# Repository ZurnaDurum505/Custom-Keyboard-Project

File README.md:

# Custom-Keyboard-Project 
I started my keyboard by starting to make the PCB using Kicad. To do the PCB I had to do the schematics first by placing switches for the keys and adding diodes on every switch so the keyboard wont start "ghosting" when multiple keys are pressed. Then i added stabilizers for each key that was going to be larger than 2U. After placing everything I started wiring the keyboard making rows and columns so i can wire them to the Pico micro controller faster, and to finish it off i added my mounting holes at the corners of my design. After that I just assigned footprints and annotated my schematics. Also if you struggle with planning out your keyboard i recommend using this website https://www.keyboard-layout-editor.com/#/ It lets you design your own keyboard by placing keys and adjusting the how many U's you want your keys to be.

After the schematics I moved to the pcb editor where draw the outline of my pcb and  reorganized my keys, diode, and stabs inside the bcb outline(because it doesn’t come to you organized in the pcb editor). After everything looked how i wanted to order to be, i placed the pico inside the b b outline with its USB port facing outside and slightly outside of my pcb outline before I started firing the pcb. I wired my keys as columns on the front board and my diode as rows on the back board, making sure to not make any of the wires in the same board side touch eachother. After the wiring was done I started making a case for it on in shape CAD. I started by making a bottom plate slightly bigger than the pcb, them making walls that are around 10-15 mm tall. Before I did the top plate, I scratched 14mm to 14mm squares on every spot a key needed to go (and also sketch holes for your stabs I eyeballed the size for mine). After that was done I made the top plate around 3mm thick closing on the pcb and extrude removed the spaces the keyholes would be from my scetch, creating holes for my keys. Before you move onto customizing yourdesign make a 5 to 10mm hole on where your pico’s port would be. After that is up to you to make it look how you want, I added another layer not covering a rectangle area where keys would be and extrude removed to carve my logo. I did this project to learn new things but also to feel the joy of creating something, I am making this keyboard to my sister who was the person who motivated me to do it and i hope anyone doing this project learns something, feels the joy of creating something, and gets motivated by it.

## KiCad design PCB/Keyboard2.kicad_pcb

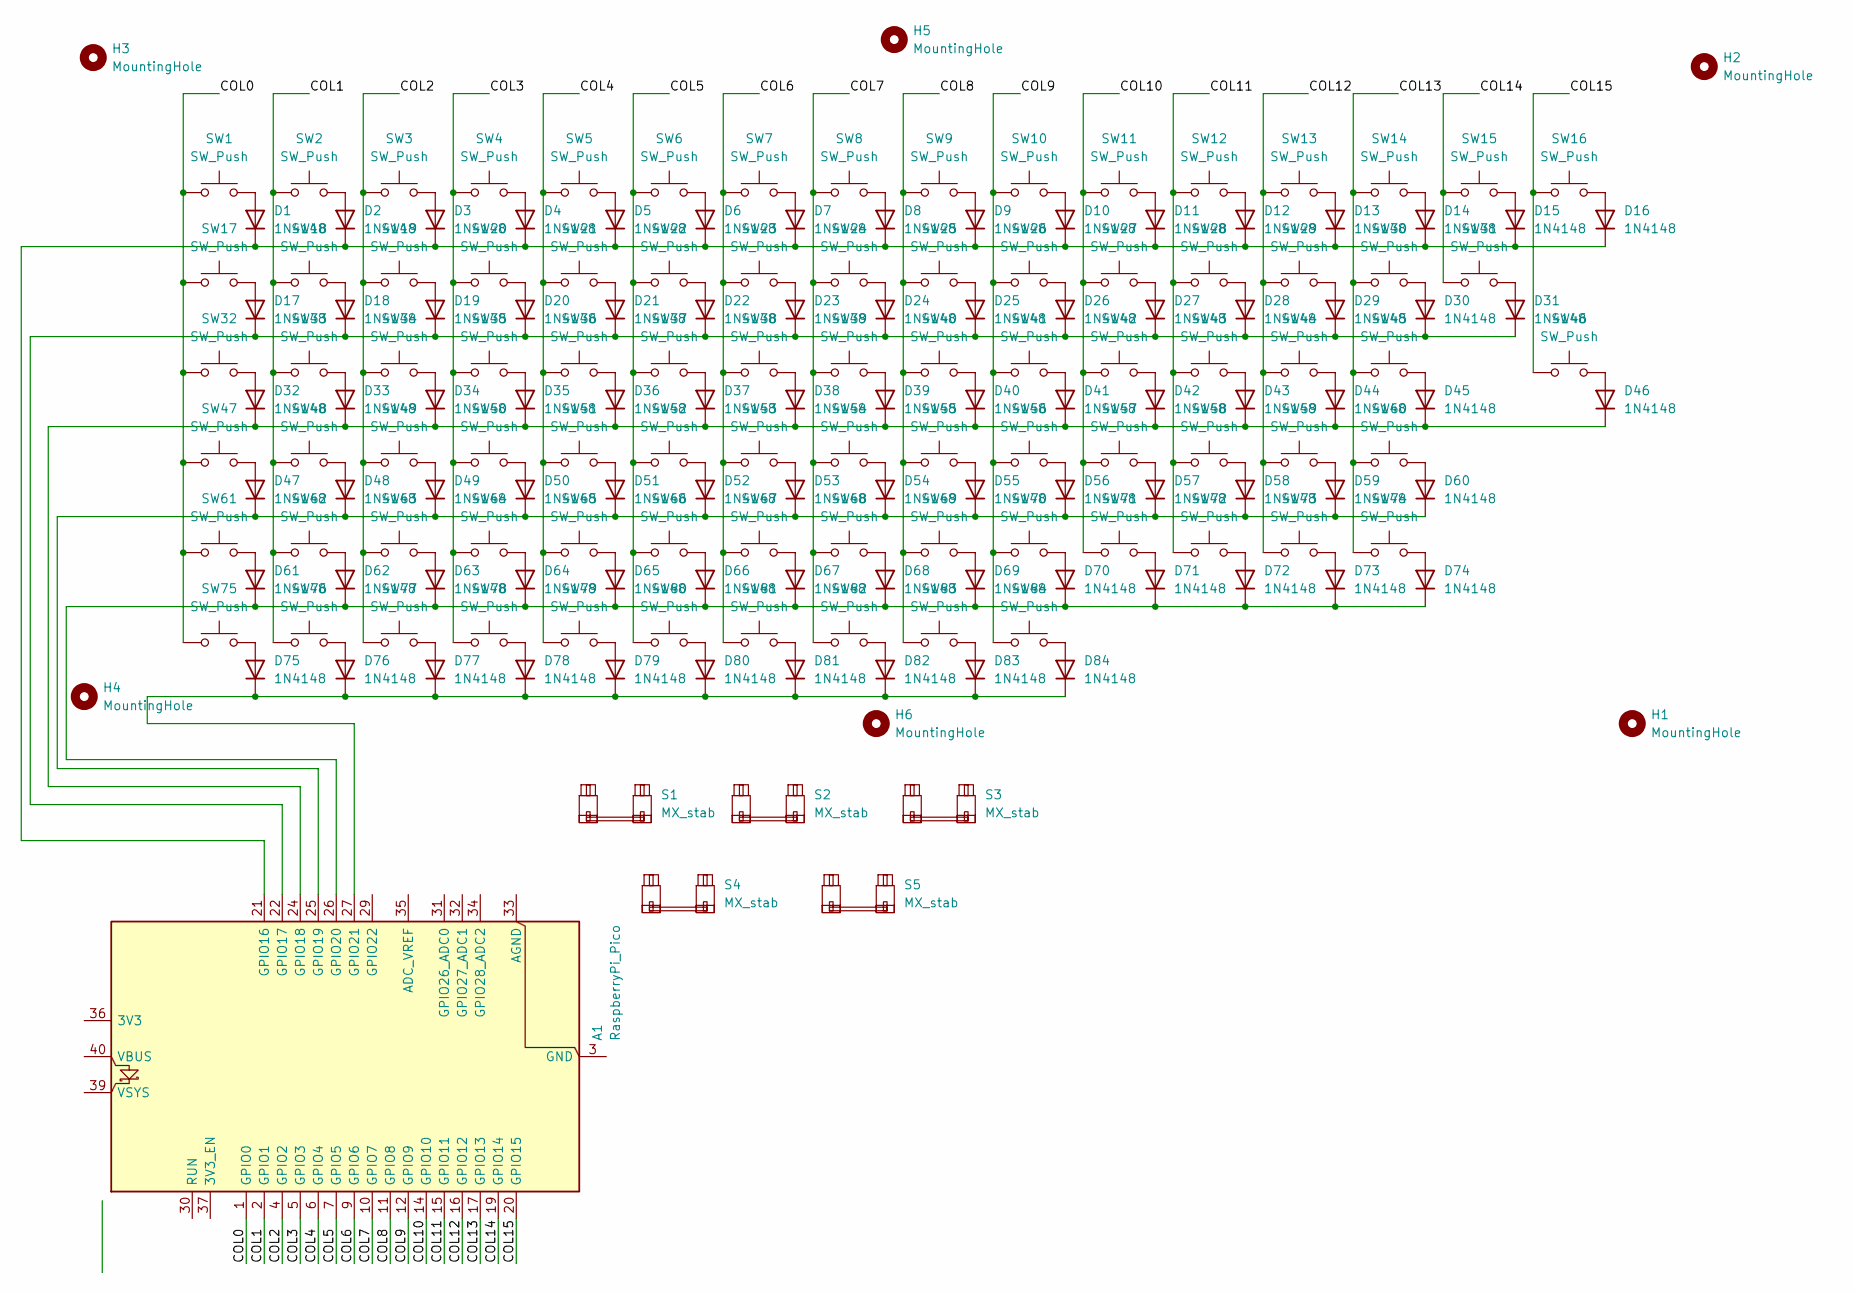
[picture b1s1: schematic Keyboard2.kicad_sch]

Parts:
A1: RaspberryPi_Pico; RaspberryPi_Pico_Common_THT
D1, D2, D3, D4, D5, D6, D7, D8, D9, D10, D11, D12, D13, D14, D15, D16, D17, D18, D19, D20, D21, D22, D23, D24, D25, D26, D27, D28, D29, D30, D31, D32, D33, D34, D35, D36, D37, D38, D39, D40, D41, D42, D43, D44, D45, D46, D47, D48, D49, D50, D51, D52, D53, D54, D55, D56, D57, D58, D59, D60, D61, D62, D63, D64, D65, D66, D67, D68, D69, D70, D71, D72, D73, D74, D75, D76, D77, D78, D79, D80, D81, D82, D83, D84: 1N4148; D_DO-35_SOD27_P7.62mm_Horizontal
H1, H2, H3, H4, H5, H6: MountingHole; MountingHole_3.2mm_M3
S1, S2, S3, S4, S5: MX_stab; STAB_MX_P_6.25u
SW1, SW2, SW3, SW4, SW5, SW6, SW7, SW8, SW9, SW10, SW11, SW12, SW13, SW14, SW15, SW16, SW17, SW18, SW19, SW20, SW21, SW22, SW23, SW24, SW25, SW26, SW27, SW28, SW29, SW30, SW31, SW32, SW33, SW34, SW35, SW36, SW37, SW38, SW39, SW40, SW41, SW42, SW43, SW44, SW45, SW46, SW47, SW48, SW49, SW50, SW51, SW52, SW53, SW54, SW55, SW56, SW57, SW58, SW59, SW60, SW61, SW62, SW63, SW64, SW65, SW66, SW67, SW68, SW69, SW70, SW71, SW72, SW73, SW74, SW75, SW76, SW77, SW78, SW79, SW80, SW81, SW82, SW83, SW84: SW_Push; SW_MX_1u

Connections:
/COL0: A1.1 (GPIO0), SW1.1, SW17.1, SW32.1, SW47.1, SW61.1, SW75.1
/COL1: A1.2 (GPIO1), SW2.1, SW18.1, SW33.1, SW48.1, SW62.1, SW76.1
/COL2: A1.4 (GPIO2), SW3.1, SW19.1, SW34.1, SW49.1, SW63.1, SW77.1
/COL3: A1.5 (GPIO3), SW4.1, SW20.1, SW35.1, SW50.1, SW64.1, SW78.1
/COL4: A1.6 (GPIO4), SW5.1, SW21.1, SW36.1, SW51.1, SW65.1, SW79.1
/COL5: A1.7 (GPIO5), SW6.1, SW22.1, SW37.1, SW52.1, SW66.1, SW80.1
/COL6: A1.9 (GPIO6), SW7.1, SW23.1, SW38.1, SW53.1, SW67.1, SW81.1
/COL7: A1.10 (GPIO7), SW8.1, SW24.1, SW39.1, SW54.1, SW68.1, SW82.1
/COL8: A1.11 (GPIO8), SW9.1, SW25.1, SW40.1, SW55.1, SW69.1, SW83.1
/COL9: A1.12 (GPIO9), SW10.1, SW26.1, SW41.1, SW56.1, SW70.1, SW84.1
/COL10: A1.14 (GPIO10), SW11.1, SW27.1, SW42.1, SW57.1, SW71.1
/COL11: A1.15 (GPIO11), SW12.1, SW28.1, SW43.1, SW58.1, SW72.1
/COL12: A1.16 (GPIO12), SW13.1, SW29.1, SW44.1, SW59.1, SW73.1
/COL13: A1.17 (GPIO13), SW14.1, SW30.1, SW45.1, SW60.1, SW74.1
/COL14: A1.19 (GPIO14), SW15.1, SW31.1
/COL15: A1.20 (GPIO15), SW16.1, SW46.1
unnamed: A1.3 (GND), A1.8 (GND), A1.13 (GND), A1.18 (GND), A1.23 (GND), A1.28 (GND), A1.38 (GND)
unnamed: A1.21 (GPIO16), D1.1 (K), D2.1 (K), D3.1 (K), D4.1 (K), D5.1 (K), D6.1 (K), D7.1 (K), D8.1 (K), D9.1 (K), D10.1 (K), D11.1 (K), D12.1 (K), D13.1 (K), D14.1 (K), D15.1 (K), D16.1 (K)
unnamed: A1.22 (GPIO17), D17.1 (K), D18.1 (K), D19.1 (K), D20.1 (K), D21.1 (K), D22.1 (K), D23.1 (K), D24.1 (K), D25.1 (K), D26.1 (K), D27.1 (K), D28.1 (K), D29.1 (K), D30.1 (K), D31.1 (K)
unnamed: A1.24 (GPIO18), D32.1 (K), D33.1 (K), D34.1 (K), D35.1 (K), D36.1 (K), D37.1 (K), D38.1 (K), D39.1 (K), D40.1 (K), D41.1 (K), D42.1 (K), D43.1 (K), D44.1 (K), D45.1 (K), D46.1 (K)
unnamed: A1.25 (GPIO19), D47.1 (K), D48.1 (K), D49.1 (K), D50.1 (K), D51.1 (K), D52.1 (K), D53.1 (K), D54.1 (K), D55.1 (K), D56.1 (K), D57.1 (K), D58.1 (K), D59.1 (K), D60.1 (K)
unnamed: A1.26 (GPIO20), D61.1 (K), D62.1 (K), D63.1 (K), D64.1 (K), D65.1 (K), D66.1 (K), D67.1 (K), D68.1 (K), D69.1 (K), D70.1 (K), D71.1 (K), D72.1 (K), D73.1 (K), D74.1 (K)
unnamed: A1.27 (GPIO21), D75.1 (K), D76.1 (K), D77.1 (K), D78.1 (K), D79.1 (K), D80.1 (K), D81.1 (K), D82.1 (K), D83.1 (K), D84.1 (K)
unnamed: D1.2 (A), SW1.2
unnamed: D2.2 (A), SW2.2
unnamed: D3.2 (A), SW3.2
unnamed: D4.2 (A), SW4.2
unnamed: D5.2 (A), SW5.2
unnamed: D6.2 (A), SW6.2
unnamed: D7.2 (A), SW7.2
unnamed: D8.2 (A), SW8.2
unnamed: D9.2 (A), SW9.2
unnamed: D10.2 (A), SW10.2
unnamed: D11.2 (A), SW11.2
unnamed: D12.2 (A), SW12.2
unnamed: D13.2 (A), SW13.2
unnamed: D14.2 (A), SW14.2
unnamed: D15.2 (A), SW15.2
unnamed: D16.2 (A), SW16.2
unnamed: D17.2 (A), SW17.2
unnamed: D18.2 (A), SW18.2
unnamed: D19.2 (A), SW19.2
unnamed: D20.2 (A), SW20.2
unnamed: D21.2 (A), SW21.2
unnamed: D22.2 (A), SW22.2
unnamed: D23.2 (A), SW23.2
unnamed: D24.2 (A), SW24.2
unnamed: D25.2 (A), SW25.2
unnamed: D26.2 (A), SW26.2
unnamed: D27.2 (A), SW27.2
unnamed: D28.2 (A), SW28.2
unnamed: D29.2 (A), SW29.2
unnamed: D30.2 (A), SW30.2
unnamed: D31.2 (A), SW31.2
unnamed: D32.2 (A), SW32.2
unnamed: D33.2 (A), SW33.2
unnamed: D34.2 (A), SW34.2
unnamed: D35.2 (A), SW35.2
unnamed: D36.2 (A), SW36.2
unnamed: D37.2 (A), SW37.2
unnamed: D38.2 (A), SW38.2
unnamed: D39.2 (A), SW39.2
unnamed: D40.2 (A), SW40.2
unnamed: D41.2 (A), SW41.2
unnamed: D42.2 (A), SW42.2
unnamed: D43.2 (A), SW43.2
unnamed: D44.2 (A), SW44.2
unnamed: D45.2 (A), SW45.2
unnamed: D46.2 (A), SW46.2
unnamed: D47.2 (A), SW47.2
unnamed: D48.2 (A), SW48.2
unnamed: D49.2 (A), SW49.2
unnamed: D50.2 (A), SW50.2
unnamed: D51.2 (A), SW51.2
unnamed: D52.2 (A), SW52.2
unnamed: D53.2 (A), SW53.2
unnamed: D54.2 (A), SW54.2
unnamed: D55.2 (A), SW55.2
unnamed: D56.2 (A), SW56.2
unnamed: D57.2 (A), SW57.2
unnamed: D58.2 (A), SW58.2
unnamed: D59.2 (A), SW59.2
unnamed: D60.2 (A), SW60.2
unnamed: D61.2 (A), SW61.2
unnamed: D62.2 (A), SW62.2
unnamed: D63.2 (A), SW63.2
unnamed: D64.2 (A), SW64.2
unnamed: D65.2 (A), SW65.2
unnamed: D66.2 (A), SW66.2
unnamed: D67.2 (A), SW67.2
unnamed: D68.2 (A), SW68.2
unnamed: D69.2 (A), SW69.2
unnamed: D70.2 (A), SW70.2
unnamed: D71.2 (A), SW71.2
unnamed: D72.2 (A), SW72.2
unnamed: D73.2 (A), SW73.2
unnamed: D74.2 (A), SW74.2
unnamed: D75.2 (A), SW75.2
unnamed: D76.2 (A), SW76.2
unnamed: D77.2 (A), SW77.2
unnamed: D78.2 (A), SW78.2
unnamed: D79.2 (A), SW79.2
unnamed: D80.2 (A), SW80.2
unnamed: D81.2 (A), SW81.2
unnamed: D82.2 (A), SW82.2
unnamed: D83.2 (A), SW83.2
unnamed: D84.2 (A), SW84.2

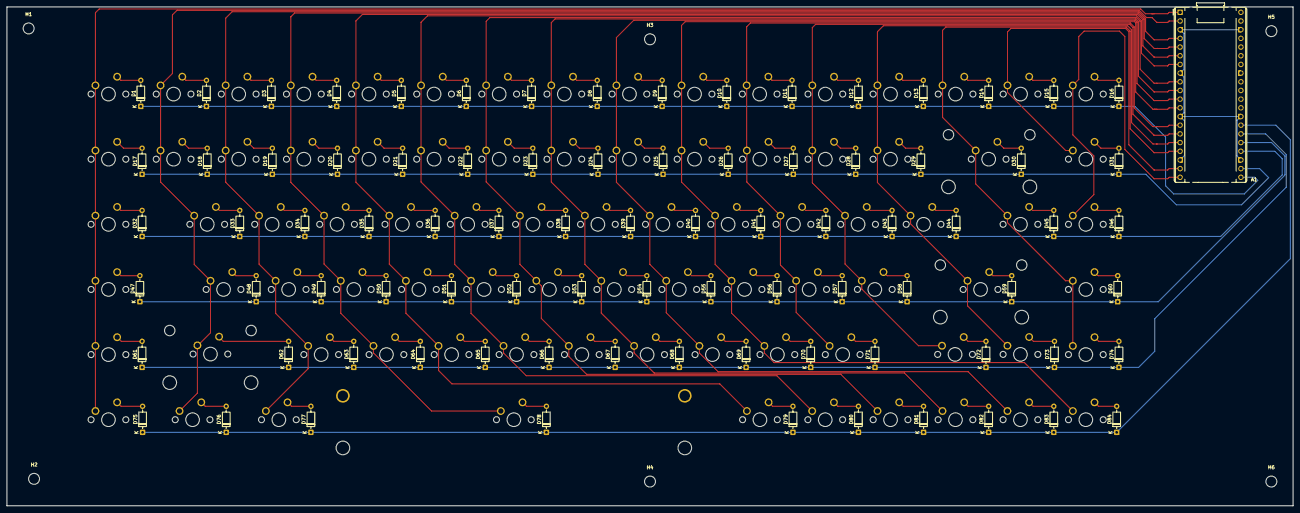
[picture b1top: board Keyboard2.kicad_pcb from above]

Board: 2 copper layers, 376.2 x 145.9 mm, 179 parts (0 on the bottom side), 107 nets.
